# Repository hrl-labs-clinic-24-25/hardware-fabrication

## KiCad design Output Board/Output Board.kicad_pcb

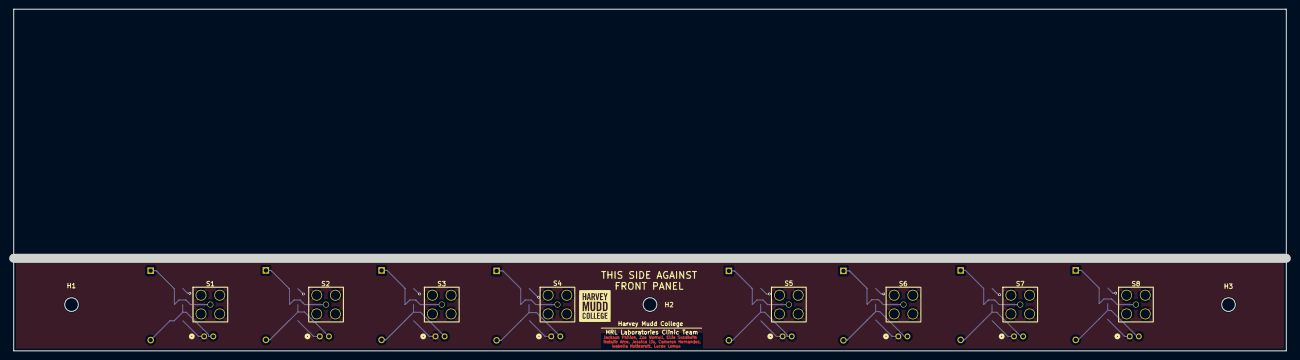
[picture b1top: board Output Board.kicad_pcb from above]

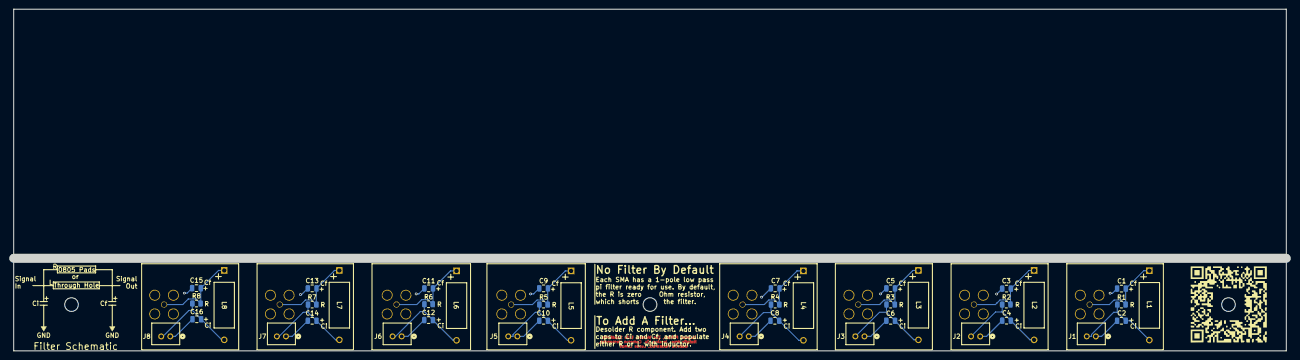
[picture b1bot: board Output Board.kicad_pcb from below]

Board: 2 copper layers, 279.4 x 73.0 mm, 52 parts (40 on the bottom side), 17 nets.

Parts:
  : LOGO; Footprint_HMC
C1, C2, C3, C4, C5, C6, C7, C8, C9, C10, C11, C12, C13, C14, C15, C16: C; C_0805_2012Metric
H1, H2, H3: MountingHole; MountingHole_3mm
J1, J2, J3, J4, J5, J6, J7, J8: B2B-PH-K-SLFSN; CONN_B2B-PH-K-SLFSN_JST
L1, L2, L3, L4, L5, L6, L7, L8: L; IND_1537R_API
R1, R2, R3, R4, R5, R6, R7, R8: 0; R_0805_2012Metric
S1, S2, S3, S4, S5, S6, S7, S8: SMA_CONNECTOR; HJ-SMA993

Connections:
GND: C1.2, C2.2, C3.2, C4.2, C5.2, C6.2, C7.2, C8.2, C9.2, C10.2, C11.2, C12.2, C13.2, C14.2, C15.2, C16.2, J1.1, J2.1, J3.1, J4.1, J5.1, J6.1, J7.1, J8.1, S1.1, S1.2, S1.4, S1.5, S2.1, S2.2, S2.4, S2.5, S3.1, S3.2, S3.4, S3.5, S4.1, S4.2, S4.4, S4.5, S5.1, S5.2, S5.4, S5.5, S6.1, S6.2, S6.4, S6.5, S7.1, S7.2, S7.4, S7.5, S8.1, S8.2, S8.4, S8.5
unnamed: C1.1, L1.1, R1.1, S1.3
unnamed: C2.1, J1.2, L1.2, R1.2
unnamed: C3.1, L2.1, R2.1, S2.3
unnamed: C4.1, J2.2, L2.2, R2.2
unnamed: C5.1, L3.1, R3.1, S3.3
unnamed: C6.1, J3.2, L3.2, R3.2
unnamed: C7.1, L4.1, R4.1, S4.3
unnamed: C8.1, J4.2, L4.2, R4.2
unnamed: C9.1, L5.1, R5.1, S5.3
unnamed: C10.1, J5.2, L5.2, R5.2
unnamed: C11.1, L6.1, R6.1, S6.3
unnamed: C12.1, J6.2, L6.2, R6.2
unnamed: C13.1, L7.1, R7.1, S7.3
unnamed: C14.1, J7.2, L7.2, R7.2
unnamed: C15.1, L8.1, R8.1, S8.3
unnamed: C16.1, J8.2, L8.2, R8.2

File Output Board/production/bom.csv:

Designator,Footprint,Quantity,Value,LCSC Part #
"C1, C10, C11, C12, C13, C14, C15, C16, C2, C3, C4, C5, C6, C7, C8, C9",0805,16,C,
"J1, J2, J3, J4, J5, J6, J7, J8",CONN_B2B-PH-K-SLFSN_JST,8,B2B-PH-K-SLFSN,
"L1, L2, L3, L4, L5, L6, L7, L8",IND_1537R_API,8,L,
"R1, R2, R3, R4, R5, R6, R7, R8",0805,8,0,
"S1, S2, S3, S4, S5, S6, S7, S8",HJ-SMA993,8,SMA_CONNECTOR,

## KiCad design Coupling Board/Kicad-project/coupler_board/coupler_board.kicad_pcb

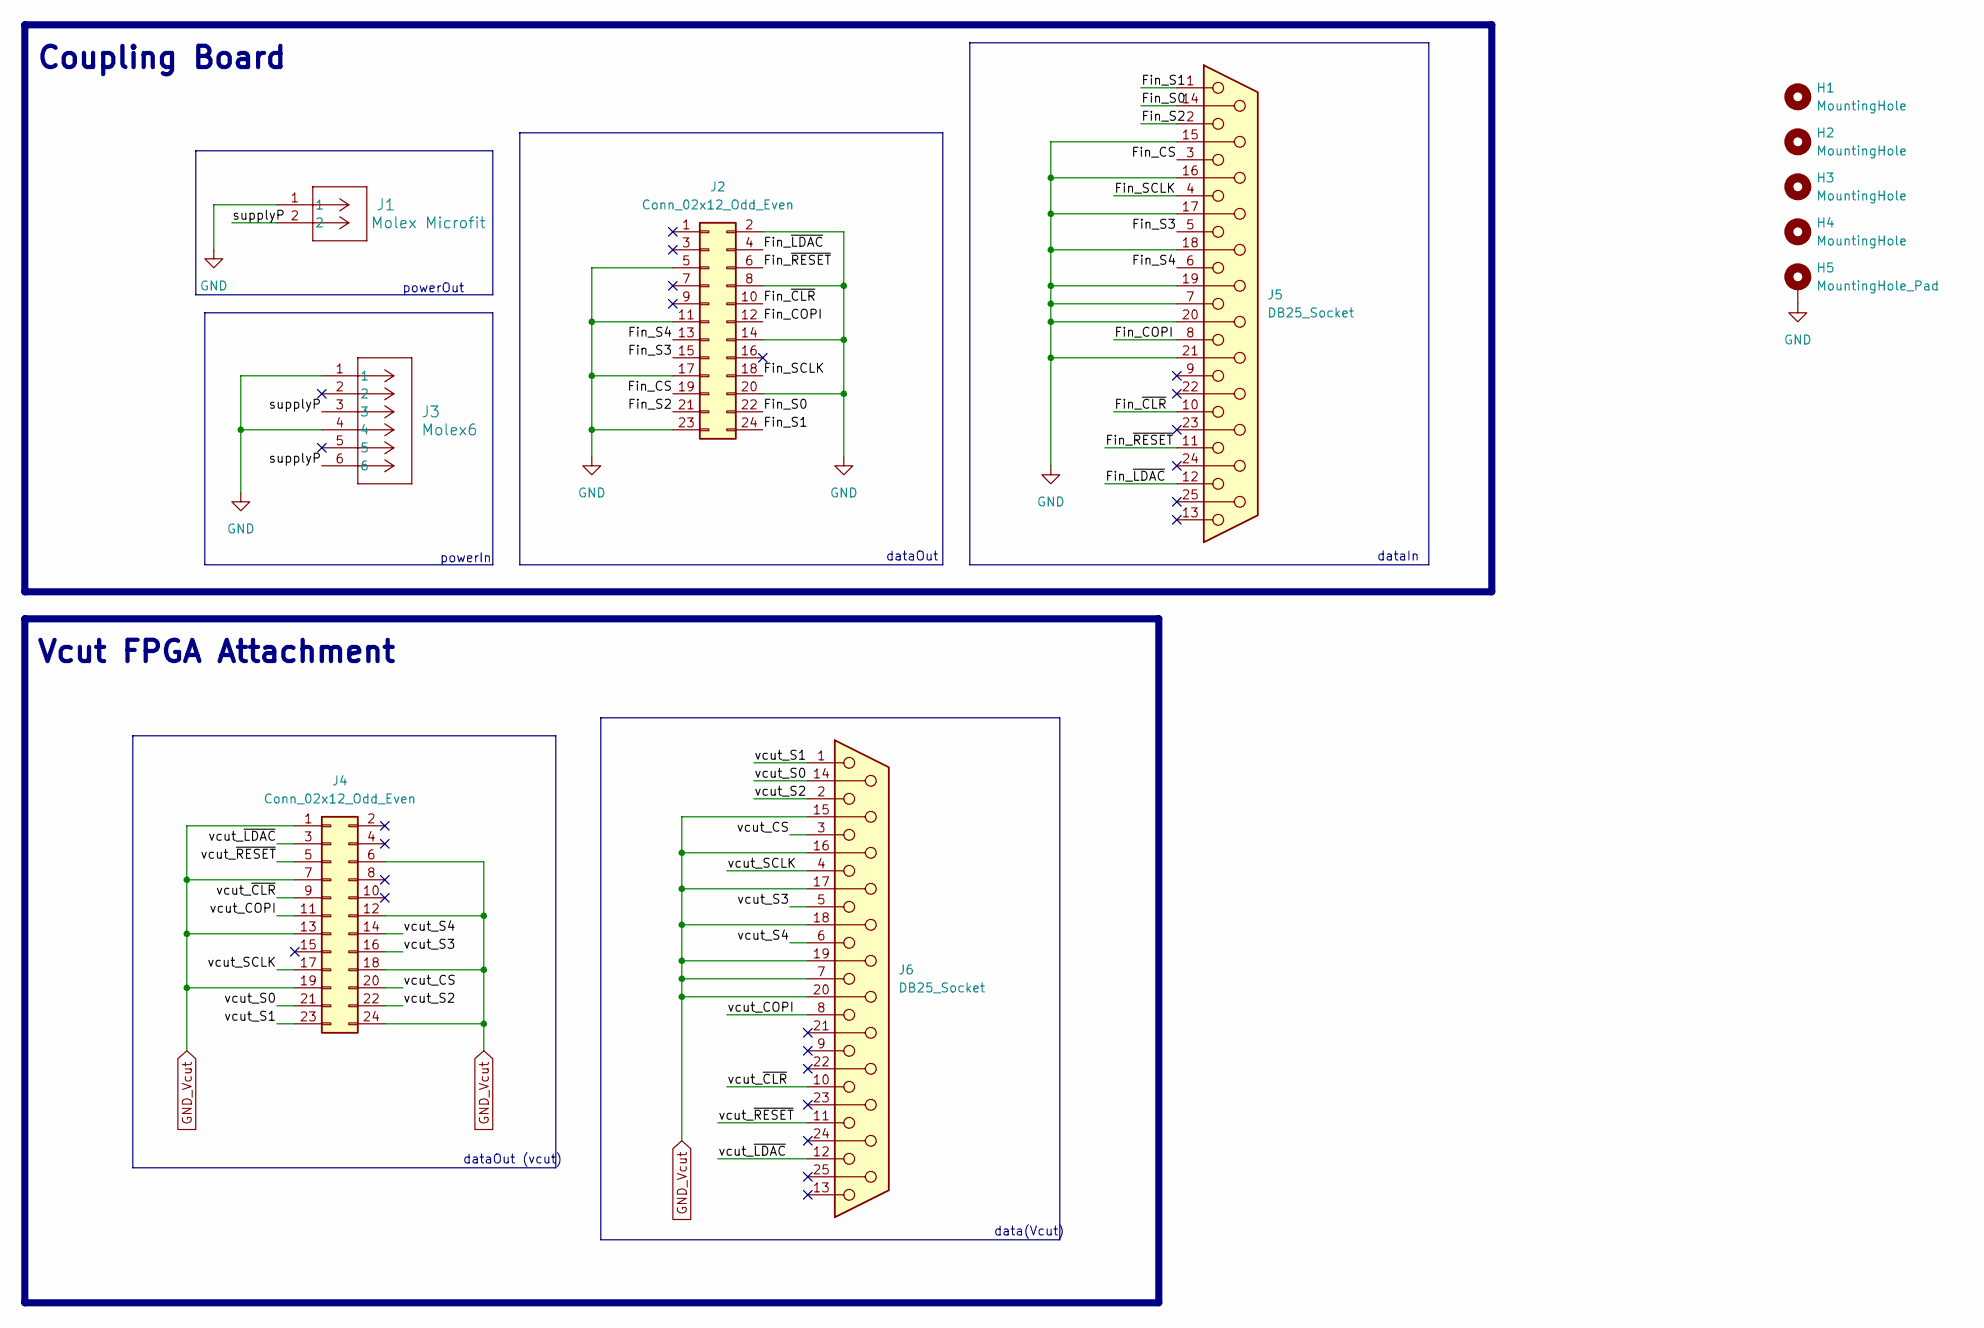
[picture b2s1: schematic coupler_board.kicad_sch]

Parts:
H1, H2, H3, H4: MountingHole; MountingHole_3.2mm_M3
H5: MountingHole_Pad; MountingHole_3.5mm_Pad
J1: Molex Microfit; CONN_SD-43650-006_02_MOL
J2: Conn_02x12_Odd_Even; IDC-Header_2x12_P2.54mm_Vertical; JLCPCB Part # C132440
J3: Molex6; CONN_SD-5566-002_06_MOL
J4: Conn_02x12_Odd_Even; PinHeader_2x12_P2.54mm_Vertical; JLCPCB Part # C132440
J5, J6: DB25_Socket; DSUB-TH_DS1034-25FUNSI44

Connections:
/Fin_COPI: J2.12, J5.8
/Fin_CS: J2.19, J5.3
/Fin_S0: J2.22, J5.14
/Fin_S1: J2.24, J5.1
/Fin_S2: J2.21, J5.2
/Fin_S3: J2.15, J5.5
/Fin_S4: J2.13, J5.6
/Fin_SCLK: J2.18, J5.4
/Fin_~CLR: J2.10, J5.10
/Fin_~LDAC: J2.4, J5.12
/Fin_~RESET: J2.6, J5.11
/supplyP: J1.2, J3.3, J3.6
/vcut_COPI: J4.11, J6.8
/vcut_CS: J4.20, J6.3
/vcut_S0: J4.21, J6.14
/vcut_S1: J4.23, J6.1
/vcut_S2: J4.22, J6.2
/vcut_S3: J4.16, J6.5
/vcut_S4: J4.14, J6.6
/vcut_SCLK: J4.17, J6.4
/vcut_~CLR: J4.9, J6.10
/vcut_~LDAC: J4.3, J6.12
/vcut_~RESET: J4.5, J6.11
GND: H5.1, J1.1, J2.2, J2.5, J2.8, J2.11, J2.14, J2.17, J2.20, J2.23, J3.1, J3.4, J5.7, J5.15, J5.16, J5.17, J5.18, J5.19, J5.20, J5.21
GND_Vcut: J4.1, J4.6, J4.7, J4.12, J4.13, J4.18, J4.19, J4.24, J6.7, J6.15, J6.16, J6.17, J6.18, J6.19, J6.20

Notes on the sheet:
dataOut (vcut)
Vcut FPGA Attachment
dataIn
dataOut
powerIn
powerOut
Coupling Board
data(Vcut)

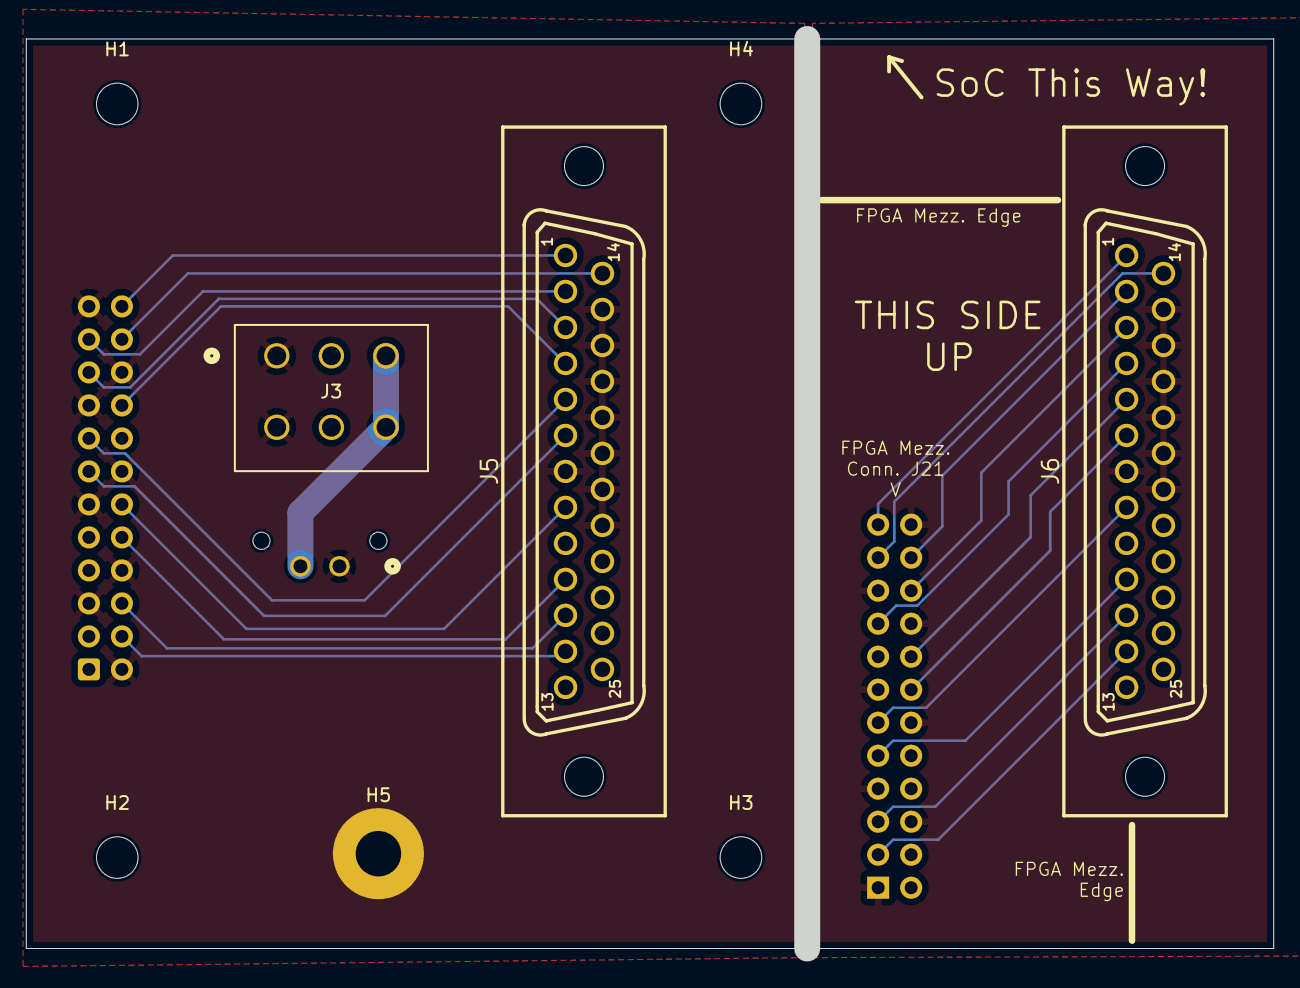
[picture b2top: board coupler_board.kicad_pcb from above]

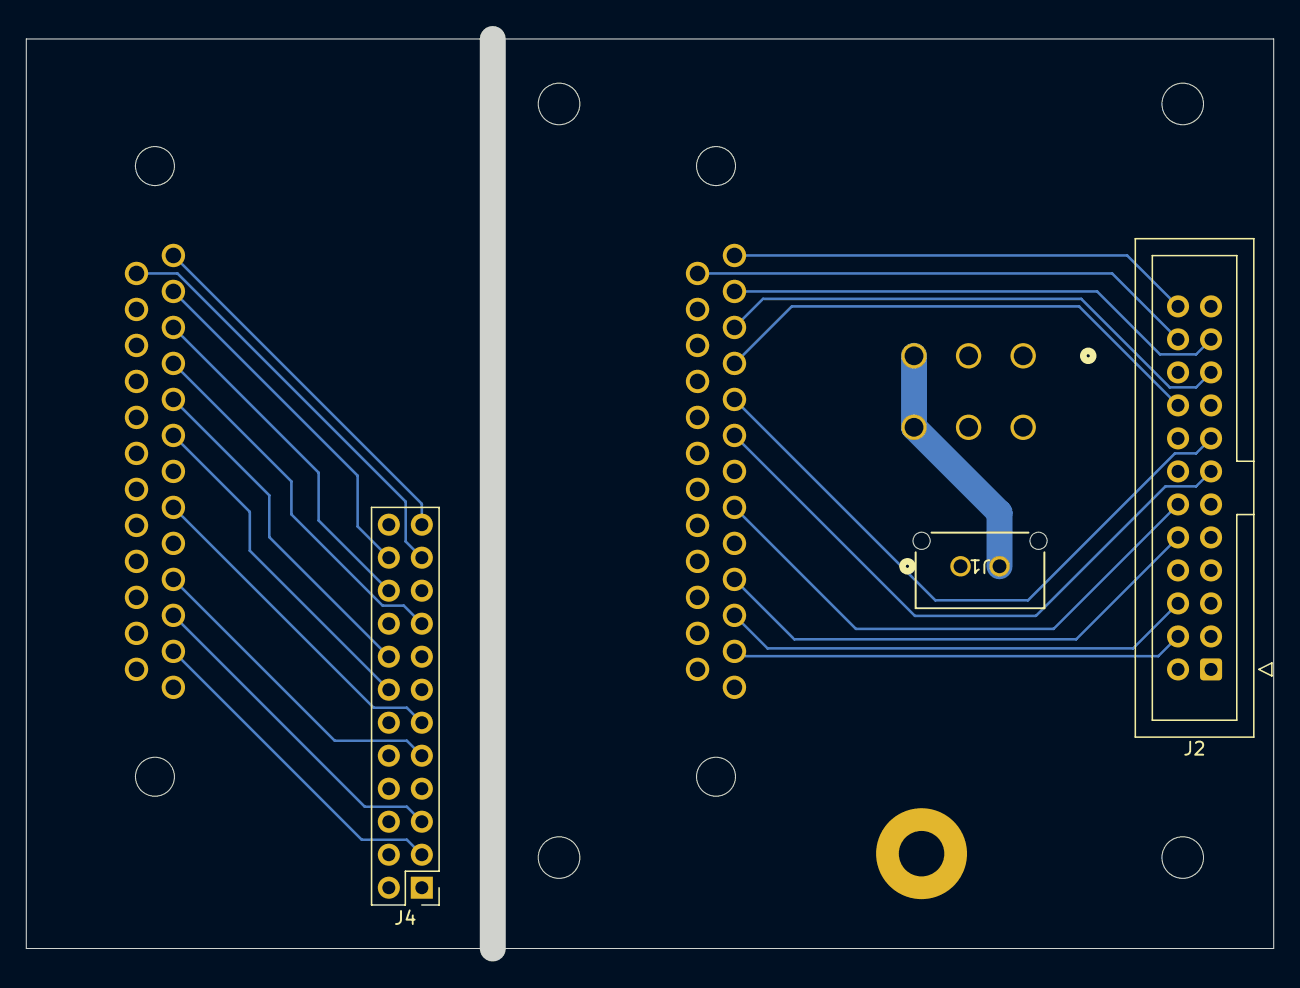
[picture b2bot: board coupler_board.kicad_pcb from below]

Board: 2 copper layers, 94.1 x 70.0 mm, 11 parts (3 on the bottom side), 25 nets.

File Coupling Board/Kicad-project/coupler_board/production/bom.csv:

Designator,Footprint,Quantity,Value,LCSC Part #
H5,MountingHole_3.5mm_Pad,1,MountingHole_Pad,
J1,CONN_SD-43650-006_02_MOL,1,Molex Microfit,
J2,IDC-Header_2x12_P2.54mm_Vertical,1,Conn_02x12_Odd_Even,C132440
J3,CONN_SD-5566-002_06_MOL,1,Molex6,
J4,PinHeader_2x12_P2.54mm_Vertical,1,Conn_02x12_Odd_Even,C132440
"J5, J6",DSUB-TH_DS1034-25FUNSI44,2,DB25_Socket,

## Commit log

2025-04-22 push coupling board, support panel, front panel
2025-04-26 Add Input Board Fab Files
2025-04-26 support panel for coupling board
2025-04-26 push only the fabrication files
2025-04-26 push only fabrication files
2025-04-26 Output Board Fabrication
2025-04-26 Final Formatting Update
2025-05-07 update coupling pcb
2025-05-08 push front panel correction
2025-05-08 pushed the support panel
2025-05-08 Internal Support STL Files
2025-05-15 Input Board V5
